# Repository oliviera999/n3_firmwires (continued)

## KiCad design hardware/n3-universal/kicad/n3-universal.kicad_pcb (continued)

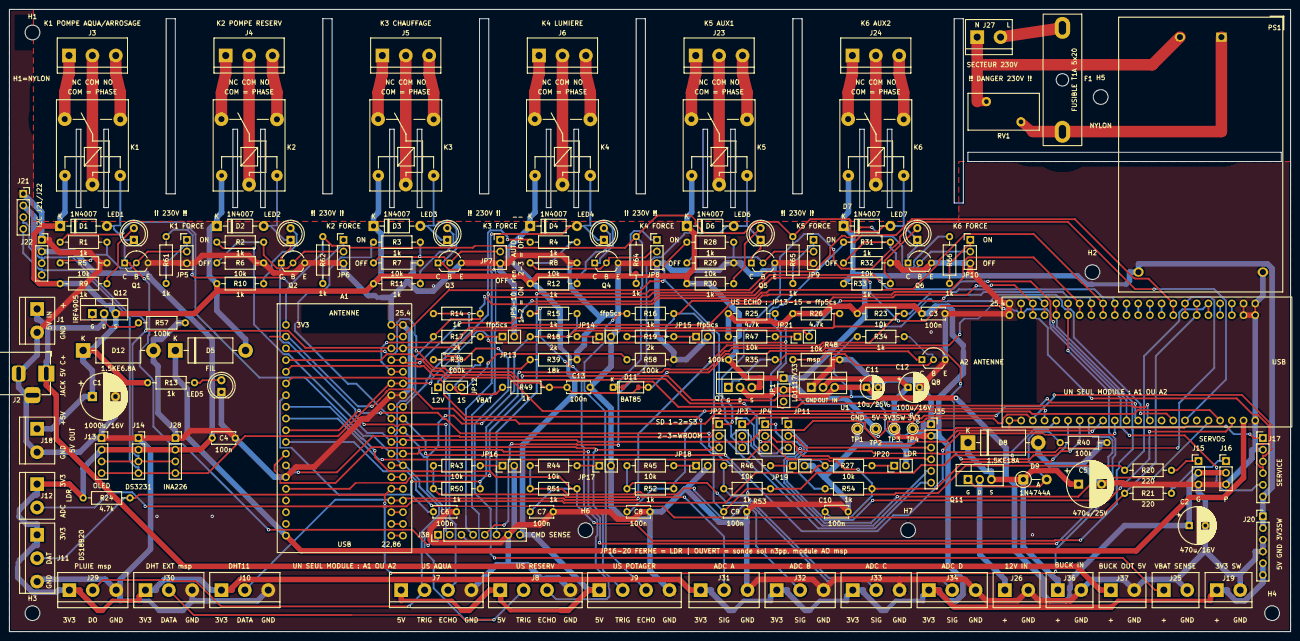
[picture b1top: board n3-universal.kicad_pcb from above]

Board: 2 copper layers, 278.0 x 135.0 mm, 179 parts (0 on the bottom side), 115 nets.

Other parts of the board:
H1, H2, H3, H4, H5, H6, H7: M3; MountingHole_3.2mm_M3

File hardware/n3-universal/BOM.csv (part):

Refs;Qte;Valeur;Empreinte;Description;Source;LCSC;Note achat
A1;1;ESP32 DevKitC 38 broches;ESP32_DevKitC_38pin;Module ESP32-WROOM-32 DevKitC 38 broches, sur 2 supports 1x19 (rangée droite à 25,4 mm, ou 22,86 mm pour un module étroit);;;
A2;1;ESP32-S3-DevKitC-1;ESP32_S3_DevKitC_1_44pin;Site optionnel ESP32-S3-DevKitC-1 44 broches, sur 2 supports 1x22 (rangée droite à 25,4 mm, ou 22,86 mm pour le DevKitC-1 officiel) — un seul module A1 OU A2;Maroc;;Shop4Makers / Moussasoft S3 N16R8 (180 DH) — ne pas importer (ANRT)
C1;1;1000u/16V;CP_Radial_D10.0mm_P5.00mm;Réservoir rail 5V (relais + servos + HC-SR04);Maroc;;électrolytique radial
C10;1;100n;C_Disc_D5.0mm_W2.5mm_P5.00mm;Filtre ADC_E;Maroc;;céramique 100 nF
C11;1;10u/25V;CP_Radial_D5.0mm_P2.50mm;Entrée LDO;Maroc;;électrolytique radial
C12;1;100u/16V;CP_Radial_D6.3mm_P2.50mm;Sortie LDO (stabilité LD1117 : >= 10 µF, électrolytique);Maroc;;électrolytique radial
C13;1;100n;C_Disc_D5.0mm_W2.5mm_P5.00mm;Filtre ADC_VBAT;Maroc;;céramique 100 nF
C2;1;470u/16V;CP_Radial_D8.0mm_P3.50mm;Réservoir du rail 5 V commuté LDO_IN côté servos (appels SG90);Maroc;;électrolytique radial
C3;1;100n;C_Disc_D5.0mm_W2.5mm_P5.00mm;Découplage 3V3 capteurs;Maroc;;céramique 100 nF
C4;1;100n;C_Disc_D5.0mm_W2.5mm_P5.00mm;Découplage 3V3 I2C;Maroc;;céramique 100 nF
C5;1;470u/25V;CP_Radial_D10.0mm_P5.00mm;Réservoir bus 12V protégé;Maroc;;électrolytique radial
C6;1;100n;C_Disc_D5.0mm_W2.5mm_P5.00mm;Filtre ADC ADC_A;Maroc;;céramique 100 nF
C7;1;100n;C_Disc_D5.0mm_W2.5mm_P5.00mm;Filtre ADC ADC_B;Maroc;;céramique 100 nF
C8;1;100n;C_Disc_D5.0mm_W2.5mm_P5.00mm;Filtre ADC ADC_C;Maroc;;céramique 100 nF
C9;1;100n;C_Disc_D5.0mm_W2.5mm_P5.00mm;Filtre ADC ADC_D;Maroc;;céramique 100 nF
D1 D2 D3 D4 D6 D7;6;1N4007;D_DO-41_SOD81_P10.16mm_Horizontal;Diode de roue libre bobine;Maroc / import;C2457;"Moussasoft ; LCSC C2457 (1N4007G MDD) — l'ancien C727 n'existe plus"
D11;1;BAT85;D_DO-35_SOD-123_Dual_P7.62mm;Clamp ADC_VBAT sur +3V3 (panneau branché par erreur sur J25) — empreinte double : BAT85/BAT42/BAT43 DO-35 OU BAT43W/BAT54 SOD-123 (LCSC C19167), un seul des deux posé;import;C19167;"DO-35 épuisé chez LCSC (BAT85 C549292 = 0) → poser la variante SOD-123 BAT43W JSCJ C19167 sur les pads CMS de l'empreinte double ; ou BAT85/BAT42 DO-35 d'une autre source"
D12;1;1.5KE6.8A;D_DO-201AD_P15.24mm_Horizontal;TVS 6,8V (Vrwm 5,8V) sur le rail +5V : surtension / inversion résiduelle;import;C412500;"TVS 6,8 V DO-201 Littelfuse (Vrwm 5,8 V, stock faible) ; repli P6KE6.8A DO-15 C409413 (pattes 0,8 mm, même trou)"
D5;1;FIL;D_DO-201AD_P15.24mm_Horizontal;"PONT DE FIL vers VIN DevKit (rev 0.2.2 : ex-1N5822 court-circuitée, +0,35 V de marge ; ne JAMAIS brancher l'USB du DevKit carte sous tension)";;;
D8;1;1.5KE18A;D_DO-201AD_P15.24mm_Horizontal;TVS 18V transitoires bus batterie (DO-201 : le P6KE est en DO-15, trop fin);import;C1666858;TVS 18 V DO-201 (Littelfuse 1.5KE18A-B) — PAS de 1.5KE15A locale (conduirait à 14,7 V)
D9;1;1N4744A;D_DO-41_SOD81_P5.08mm_Vertical_AnodeUp;Zener 15V grille-source de Q11 (K=source, A=grille) : VGS borné à -15 V;import;C238928;zener 15 V DO-41
F1;1;T1A 5x20;Fuse_5x20_Universal;Fusible entrée secteur du module alim (temporisé 1A) — porte-fusible à capot;import;C3131;porte-fusible 5x20 à capot BLX-A Xucheng C3131 (pas 22,0 ±0,5 mesuré sur sa fiche LCSC, fentes 3 mm de l'empreinte) ou Multicomp MC000830 / Schurter 0031.8201 (22,5-22,6) + cartouche T1A
H1;1;M3;MountingHole_3.2mm_M3;Trou de fixation M3 — H1 : VIS NYLON OBLIGATOIRE (tête métal à <5 mm du 230V);Maroc;;vis M3 (nylon pour H1/H5)
H2 H3 H4 H6 H7;5;M3;MountingHole_3.2mm_M3;Trou de fixation M3;Maroc;;vis M3 (nylon pour H1/H5)
H5;1;M3;MountingHole_3.2mm_M3;Trou de fixation M3 — H5 : VIS NYLON OBLIGATOIRE (entre les pistes N et L du coin secteur);Maroc;;vis M3 (nylon pour H1/H5)
J1;1;Bornier_5.08;TerminalBlock_bornier-2_P5.08mm;Entrée 5V alternative (bornier, 1=+5V 2=GND) — protégée contre l'inversion par Q12;Maroc;;KF128 / KF301 pas 5,08 (Moussasoft 4 DH, Shop4Makers)
J10;1;Bornier_5.08;TerminalBlock_bornier-3_P5.08mm;DHT11/DHT22 (1=3V3 2=DATA 3=GND) — fils nus + embouts;Maroc;;KF128 / KF301 pas 5,08 (Moussasoft 4 DH, Shop4Makers)
J11;1;Bornier_5.08;TerminalBlock_bornier-3_P5.08mm;Sonde DS18B20 étanche (1=3V3 2=DATA 3=GND);Maroc;;KF128 / KF301 pas 5,08 (Moussasoft 4 DH, Shop4Makers)
J12;1;Bornier_5.08;TerminalBlock_bornier-2_P5.08mm;LDR déportée entre 3V3 et l'ADC (1=3V3 2=ADC);Maroc;;KF128 / KF301 pas 5,08 (Moussasoft 4 DH, Shop4Makers)
J13;1;Support OLED;PinSocket_1x04_P2.54mm_Vertical;OLED SSD1306 128x64 I2C 0x3C (1=GND 2=VCC 3=SCL 4=SDA);Maroc;;barrette femelle 2,54 sécable (Moussasoft 6 DH)
J14;1;Support I2C ext;PinSocket_1x04_P2.54mm_Vertical;Extension I2C — ex. module DS3231 (1=GND 2=VCC 3=SCL 4=SDA);Maroc;;barrette femelle 2,54 sécable (Moussasoft 6 DH)
J15;1;Header servo;PinHeader_1x03_P2.54mm_Vertical;Servo GROS (1=SIG 2=LDO_IN 3=GND) — rev 0.2.2 : +5V COMMUTE par Q7 (JP1 fermé = permanent);Maroc;;barrette mâle 2,54 sécable (Moussasoft / Shop4Makers)
J16;1;Header servo;PinHeader_1x03_P2.54mm_Vertical;Servo PETITS (1=SIG 2=LDO_IN 3=GND) — rev 0.2.2 : +5V COMMUTE par Q7 (JP1 fermé = permanent);Maroc;;barrette mâle 2,54 sécable (Moussasoft / Shop4Makers)
J17;1;Header service;PinHeader_1x06_P2.54mm_Vertical;Header service (1=3V3 2=GND 3=EN 4=RX0 5=TX0 6=+5V) — tous les autres GPIO sont consommés par la carte universelle;Maroc;;barrette mâle 2,54 sécable (Moussasoft / Shop4Makers)
J18;1;Bornier_5.08;TerminalBlock_bornier-2_P5.08mm;Distribution 5V (1=+5V 2=GND);Maroc;;KF128 / KF301 pas 5,08 (Moussasoft 4 DH, Shop4Makers)
J19;1;Bornier_5.08;TerminalBlock_bornier-2_P5.08mm;Distribution 3V3 capteurs — rail COMMUTE (1=+3V3_SW 2=GND);Maroc;;KF128 / KF301 pas 5,08 (Moussasoft 4 DH, Shop4Makers)
J2;1;Jack 5.5/2.1;BarrelJack_Horizontal;Entrée 5V (jack DC-005 ~2,5 A, centre = +, ouverture bord gauche);Maroc;;jack DC-005 standard
J20;1;Header alim;PinHeader_1x06_P2.54mm_Vertical;Rail Dupont (1-2=+5V 3-4=GND 5-6=+3V3_SW);Maroc;;barrette mâle 2,54 sécable (Moussasoft / Shop4Makers)
J21;1;Support I2C libre;PinSocket_1x04_P2.54mm_Vertical;Port I2C libre 2 (1=GND 2=VCC 3=SCL 4=SDA);Maroc;;barrette femelle 2,54 sécable (Moussasoft 6 DH)
J22;1;Support I2C libre;PinSocket_1x04_P2.54mm_Vertical;Port I2C libre 3 (1=GND 2=VCC 3=SCL 4=SDA);Maroc;;barrette femelle 2,54 sécable (Moussasoft 6 DH)
J25;1;Bornier_5.08;TerminalBlock_bornier-2_P5.08mm;Sonde batterie (1=VBAT+ 2=GND) — 1S ou bus 12V selon profil;Maroc;;KF128 / KF301 pas 5,08 (Moussasoft 4 DH, Shop4Makers)
J26;1;Bornier_5.08;TerminalBlock_bornier-2_P5.08mm;Entrée bus 12V (1=+12V APRES fusible lame externe 7,5-10A 2=GND);Maroc;;KF128 / KF301 pas 5,08 (Moussasoft 4 DH, Shop4Makers)
J27;1;Bornier_5.08;TerminalBlock_bornier-2_P5.08mm;ENTREE SECTEUR 230V (1=N 2=L) — ZONE DANGER;Maroc;;KF128 / KF301 pas 5,08 (Moussasoft 4 DH, Shop4Makers)
J28;1;Support I2C libre;PinSocket_1x04_P2.54mm_Vertical;Port I2C libre 4 — INA226 (1=GND 2=VCC 3=SCL 4=SDA);Maroc;;barrette femelle 2,54 sécable (Moussasoft 6 DH)
J29;1;Bornier_5.08;TerminalBlock_bornier-3_P5.08mm;Module pluie DO msp (1=3V3_SW 2=DO 3=GND) — net US1, rôles disjoints;Maroc;;KF128 / KF301 pas 5,08 (Moussasoft 4 DH, Shop4Makers)
J23 J24 J3 J4 J5 J6;6;Bornier_5.08;TerminalBlock_bornier-3_P5.08mm;Bornier charge 230V (1=NC 2=COM 3=NO);Maroc;;KF128 / KF301 pas 5,08 (Moussasoft 4 DH, Shop4Makers)
J30;1;Bornier_5.08;TerminalBlock_bornier-3_P5.08mm;DHT externe msp (1=3V3_SW 2=DATA 3=GND) — net US2, rôles disjoints;Maroc;;KF128 / KF301 pas 5,08 (Moussasoft 4 DH, Shop4Makers)
J31;1;Bornier_5.08;TerminalBlock_bornier-3_P5.08mm;Entrée analogique ADC_A (1=3V3_SW 2=SIG 3=GND) — LDR msp / sonde sol n3pp;Maroc;;KF128 / KF301 pas 5,08 (Moussasoft 4 DH, Shop4Makers)
J32;1;Bornier_5.08;TerminalBlock_bornier-3_P5.08mm;Entrée analogique ADC_B (1=3V3_SW 2=SIG 3=GND) — LDR msp / sonde sol n3pp;Maroc;;KF128 / KF301 pas 5,08 (Moussasoft 4 DH, Shop4Makers)
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
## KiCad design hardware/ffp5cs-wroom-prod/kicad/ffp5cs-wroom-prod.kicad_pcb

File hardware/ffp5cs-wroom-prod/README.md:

# Carte porteuse ffp5cs `wroom-prod` (KiCad)

Plan PCB **généré depuis le code du firmware** `ffp5cs` (env PlatformIO `wroom-prod`,
`-DBOARD_WROOM`) : une **carte porteuse (carrier board)** pour module **ESP32 DevKit V1
30 broches** qui intègre tout le câblage aujourd'hui réalisé « en volant » — relais,
adaptation de niveau des HC-SR04, pull-ups, borniers.

> 🔀 **Bi-module depuis la rev 0.6** : la carte offre un **second site A2** pour un
> **ESP32-S3-DevKitC-1 (44 broches)** — on peuple **UN SEUL** module, A1 (WROOM) **ou**
> A2 (S3). Chaque net fonctionnel touche les deux sites ; côté S3 le firmware se
> compile avec `-DPINMAP_S3_CARRIER` (env `wroom-s3-carrier-test`, section carrier de
> `ffp5cs/include/pins.h`). Source de vérité S3 : `pinmap_s3_carrier.json`. Le header
> **J20** expose les GPIO libres du S3 (dont AUX1=IO47 / AUX2=IO42, pendants de J17).
> ⚠️ Ne PAS flasher un env `carrier` sur le système S3 historique câblé main (ni
> l'inverse) : les cartographies diffèrent (corrections strapping/PSRAM/LED RGB).

```
pinmap.json                  Source de vérité site A1 (broches ← ffp5cs/include/pins.h, section WROOM)
pinmap_s3_carrier.json       Source de vérité site A2 (← pins.h, section PINMAP_S3_CARRIER)
kicad/ffp5cs-wroom-prod.kicad_pro / .kicad_sch / .kicad_pcb   Projet KiCad (format v8, ouvrable KiCad 8/9/10)
BOM.csv                      Nomenclature (séparateur ;)
exports/gerbers-*.zip        Fichiers de fabrication (Gerbers + perçages Excellon)
exports/schema.pdf, pcb-*.svg   Rendus pour revue sans KiCad
fritzing/*.fzz               Vue breadboard du câblage (Fritzing >= 1.0)
generator/generate.py        Régénère schéma + PCB (non routé) + BOM depuis pinmap.json
generator/generate_fritzing.py  Régénère le .fzz de câblage
generator/footprints/        Empreintes officielles KiCad 8.0.9 vendorées (+ empreinte DevKit maison)
tools/check_pinmap_vs_firmware.py   Garde anti-dérive code ↔ plan
```

## Ce que couvre la carte (extrait du firmware)

| Fonction (code) | GPIO | Réalisation sur la carte |
|---|---|---|
| `Pins::POMPE_AQUA` (`actuators.h`, actif HAUT) | 16 | Relais K1 SRD-05 + BC337, bornier NO/COM/NC |
| `Pins::POMPE_RESERV` | 18 | Relais K2, idem |
| `Pins::RADIATEURS` | 2 | Relais K3, idem (strapping → pull-down base) |
| `Pins::LUMIERE` | 15 | Relais K4, idem (strapping) |
| `Pins::SERVO_GROS` | 12 | Header servo J15, série 220 Ω + **pull-down 10k obligatoire** (MTDI) |
| `Pins::SERVO_PETITS` | 13 | Header servo J16, série 220 Ω |
| `Pins::ULTRASON_AQUA/TANK/POTA` (mono-broche TRIG=ECHO, `sensor_ultrasonic.cpp`) | 4 / 19 / 33 | JST 4 pts J7-J9, écho 5 V → 3,3 V par pont 1k/2k |
| `Pins::DHT_PIN` (DHT11, `-DUSE_DHT22` en option) | 27 | JST 3 pts J10 + pull-up 10k |
| `Pins::ONE_WIRE_BUS` (DS18B20) | 26 | Bornier J11 + pull-up 4,7k |
| `Pins::LUMINOSITE` (ADC1, entrée seule) | 34 | Bornier J12 pour LDR déportée + 10k vers GND |
| `Pins::I2C_SDA/SCL` — OLED SSD1306 0x3C (`FEATURE_OLED=1`) | 21 / 22 | Support J13 (GND/VCC/SCL/SDA) + pull-ups 4,7k |
| Extension I2C : **3 ports libres** (DS3231, capteurs…) | 21 / 22 | Supports J14, J18, J19 (même brochage GND/VCC/SCL/SDA) |
| GPIO libres (5, 14, 17, 23, 25, 32, 35) + EN | — | Header J17 |

Alimentation : **5 V / 3 A** (jack 5,5/2,1 centre + OU bornier), condensateur réservoir
1000 µF, LED de présence. Le DevKit est alimenté par VIN **à travers une Schottky
1N5822** : on peut brancher l'USB (flash/debug) alim 5 V connectée sans retour de courant.
Les capteurs logiques (DHT, DS18B20, LDR, OLED) sont sur le **3V3 du DevKit** ;
HC-SR04, servos et relais sur le rail 5 V.

## Choix de conception (et pourquoi)

- **Carrier board plutôt que carte à ESP32 soudé** : le module `esp32dev` reste flashable
  par son USB (`pio run -e wroom-prod -t upload`), remplaçable en 10 s, et on évite tout
  le circuit USB-UART/auto-program. 100 % traversant → soudable à la main, fabricable
  partout (JLCPCB/PCBWay, 2 couches, 150 × 100 mm).
- **Relais commandés actif-HAUT** via NPN : conforme à `actuators.h`
  (`on()` → `digitalWrite(HIGH)`). Ne PAS utiliser un module relais du commerce
  actif-BAS sur ces sorties sans adaptation.
- **Broches de strapping** : GPIO2 et GPIO15 (relais) ont un pull-down 10k sur la base du
  transistor → niveau bas au boot, flash série non perturbé. GPIO12 (MTDI, servo gros) a
  un pull-down 10k dédié (R22) : un niveau haut au boot sélectionnerait un VDD_SDIO à
  1,8 V et **brickerait le démarrage**.
- **HC-SR04 en mono-broche** : le firmware pilote TRIG et lit ECHO sur le même GPIO.
  Câblage par canal : GPIO —(direct)— TRIG ; ECHO —1k— GPIO ; GPIO —2k— GND.
  L'écho 5 V est ramené à ~3,3 V, le trigger 3,3 V est accepté par le capteur alimenté en 5 V.
- **GPIO34 entrée seule, sans pull-up interne** : pont diviseur LDR obligatoire sur la
  carte (LDR déportée entre 3V3 et l'entrée, 10k vers GND).
- **RX0/TX0 laissés libres** (non routés) : réservés à l'USB-UART du module.
- **3 ports I2C libres** (J14/J18/J19) en plus de l'OLED : avec les pull-ups 4,7 k
  déjà en place, 3-4 modules simultanés sont confortables (adresses différentes,
  bus total < ~50 cm) — au-delà, réduire les pull-ups à 2,2 k.

## À vérifier avant fabrication (limites connues)

1. **Entraxe des modules** : l'empreinte A1 suppose un DevKit V1 **30 broches, rangées
   espacées de 25,4 mm** (2 × supports 1×15). Mesurer votre exemplaire ; les variantes
   38 broches (DevKitC) ont un autre brochage → adapter `generate.py` (table `DEVKIT_A/B`).
   L'empreinte A2 suppose un ESP32-S3-DevKitC-1 **44 broches, rangées espacées de
   22,86 mm** (2 × supports 1×22) — vérifier entraxe ET ordre des broches sur
   l'exemplaire réel (tables `S3_LEFT/S3_RIGHT`) avant de souder les supports.
2. **Routage (rev 0.6, dimensionné 12/24 V)** : PCB routé par `generator/route_lv.py`
   (freerouting + vias de couture GND + reliefs thermiques) avec des
   **classes de nets** — contacts relais NO/COM/NC en **2 mm** (≈ 5-6 A continus en
   cuivre 1 oz, marge correcte jusqu'à ~8 A en pointe), rails +5V/VIN/GND en
   **1,2 mm**, signaux 0,4 mm. DRC KiCad 8 : 0 violation, 0 non-connecté ; Gerbers
   dans `exports/`. **Le 230 V reste interdit sur cette carte** (isolement non prévu :
   plans de masse proches des contacts, pas de fentes ni de zone secteur dédiée) —
   la sérigraphie le rappelle près des borniers. Pour du secteur, piloter des modules
   relais/contacteurs 230 V déportés. NB : `generate.py` régénère un PCB **non
   routé** — ne pas régénérer par-dessus `kicad/` sans vouloir perdre le routage.
3. **Relais NO/NC** : mapping issu du couple symbole/empreinte officiel KiCad
   (SANYOU SRD Form C : bobine 2-5, COM 1, NO 3, NC 4). Contrôler à l'ohmmètre au
   premier montage avant de brancher une charge.
4. **ERC/DRC** : les étiquettes locales alimentent les nets (pas de power-flags) ; l'ERC
   émet des avertissements « input power pin not driven », sans conséquence.

## Corrections rev 0.5

- **Supports du DevKit dans la BOM** (ligne « A1 (supports) » : 2 barrettes femelles
  1×15) — jusque-là seulement mentionnés en description.
- **Zone dégagée sous l'antenne WiFi** : keepout cuivre (pistes/vias/pour) sur les
  deux faces sous le débord antenne du module, note sérigraphiée déplacée côté antenne.
- **Checker étendu** : `tools/check_pinmap_vs_firmware.py` fige désormais aussi la
  topologie des canaux HC-SR04 (JST 1=+5V 2=GPIO 3=ECHO 4=GND, 1 k série écho,
  2 k pull-down) — le câblage capteur ne peut plus dériver silencieusement.
- GPIO 23/25 : déclarés `AUX1`/`AUX2` dans `pinmap.json` (firmware ≥ v15.26) ; sur
  cette carte ils restent en breakout J17 (piloter des modules relais externes) —
  les relais AUX embarqués sont sur la variante 230 V.

## Vue Fritzing (câblage de prototype)

`fritzing/ffp5cs-wroom-prod-cablage.fzz` (Fritzing ≥ 1.0) montre le **câblage
breadboard** périphériques ↔ DevKit : HC-SR04 + ponts 1k/2k, DS18B20, LDR, servos,
pull-ups, avec le code couleur rouge = 5 V, orange = 3V3, noir = GND. Le DevKit, le
DHT11, l'OLED et les sorties relais sont figurés par des **headers génériques
étiquetés** (pas de pièce core fidèle dans Fritzing) — survoler une pièce affiche son
titre avec l'ordre des broches. Fichier vérifié à l'ouverture (« Routing completed »,
aucune pièce manquante) ; les positions se réarrangent librement, les connexions
suivent. Le projet KiCad reste la référence pour la fabrication.

## Régénérer / vérifier

```bash
cd hardware/ffp5cs-wroom-prod
python3 generator/generate.py                 # schéma + PCB placé (NON routé) + BOM
python3 generator/route_lv.py                 # routage complet + vérifications
python3 generator/tidy_silkscreen.py   # sérigraphie : repères vs étiquettes
python3 generator/export_fab.py        # zip Gerbers prêt JLCPCB
python3 tools/check_pinmap_vs_firmware.py     # cohérence pins.h (WROOM) ↔ pinmap ↔ schéma ↔ PCB
```

Toute modification de `ffp5cs/include/pins.h` (section WROOM) doit être répercutée dans
`pinmap.json` puis régénérée — le checker échoue (exit ≠ 0) tant que les trois ne sont
pas alignés. ⚠️ La régénération **écrase** `kicad/` : une fois le routage manuel commencé,
faire les retouches dans KiCad et cesser de régénérer (ou porter les retouches dans
`generate.py`).

## Licences

Les empreintes de `generator/footprints/` proviennent de la
[bibliothèque officielle KiCad](https://gitlab.com/kicad/libraries/kicad-footprints)
(tag 8.0.9), licence CC-BY-SA 4.0 avec exception d'usage pour les designs ;
`ESP32_DevKit_V1_30pin.kicad_mod` est généré par `generate.py`.

Commander la carte : voir **[../COMMANDE_JLCPCB.md](../COMMANDE_JLCPCB.md)**.

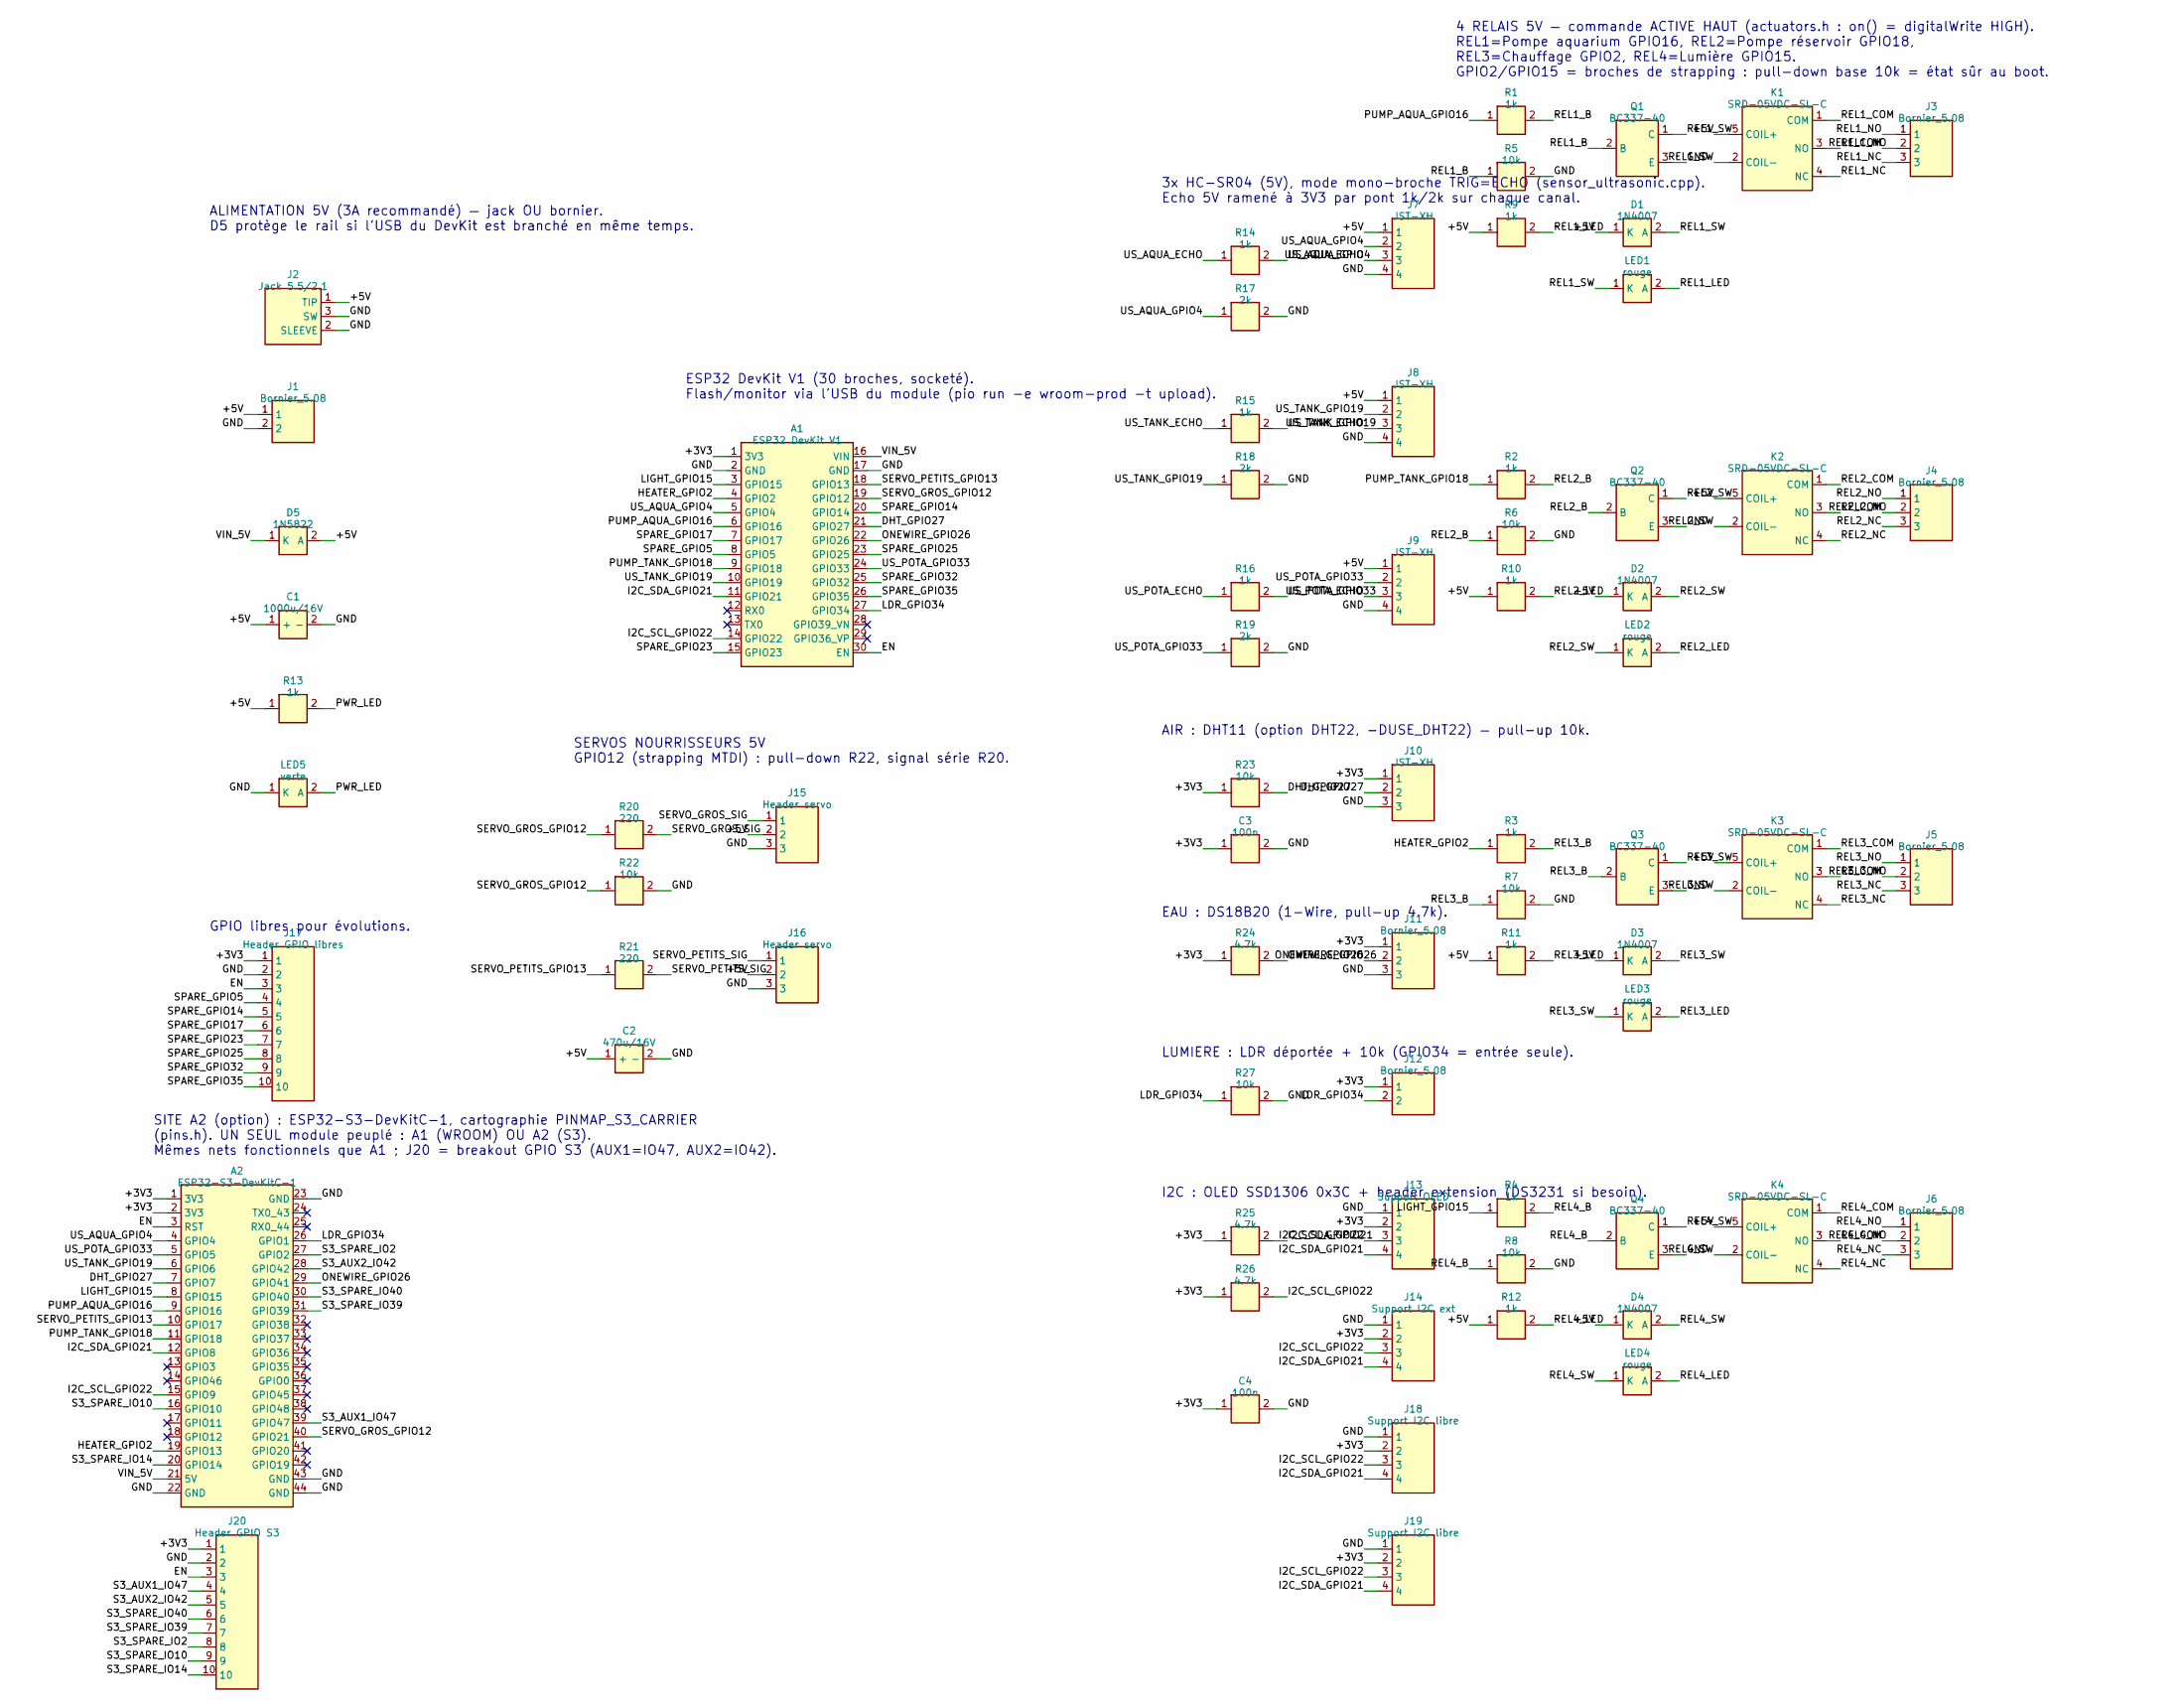
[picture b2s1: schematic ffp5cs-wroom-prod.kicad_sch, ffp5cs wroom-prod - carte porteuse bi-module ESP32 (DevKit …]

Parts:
A1: ESP32 DevKit V1; ESP32_DevKit_V1_30pin
A2: ESP32-S3-DevKitC-1; ESP32_S3_DevKitC_1_44pin
C1: 1000u/16V; CP_Radial_D10.0mm_P5.00mm
C2: 470u/16V; CP_Radial_D8.0mm_P3.50mm
C3, C4: 100n; C_Disc_D5.0mm_W2.5mm_P5.00mm
D1, D2, D3, D4: 1N4007; D_DO-41_SOD81_P10.16mm_Horizontal
D5: 1N5822; D_DO-201AD_P15.24mm_Horizontal
J1, J12: Bornier_5.08; TerminalBlock_bornier-2_P5.08mm
J2: Jack 5.5/2.1; BarrelJack_Horizontal
J3, J4, J5, J6, J11: Bornier_5.08; TerminalBlock_bornier-3_P5.08mm
J7, J8, J9: JST-XH; JST_XH_B4B-XH-A_1x04_P2.50mm_Vertical
J10: JST-XH; JST_XH_B3B-XH-A_1x03_P2.50mm_Vertical
J13: Support OLED; PinSocket_1x04_P2.54mm_Vertical
J14: Support I2C ext; PinSocket_1x04_P2.54mm_Vertical
J15, J16: Header servo; PinHeader_1x03_P2.54mm_Vertical
J17: Header GPIO libres; PinHeader_1x10_P2.54mm_Vertical
J18, J19: Support I2C libre; PinSocket_1x04_P2.54mm_Vertical
J20: Header GPIO S3; PinHeader_1x10_P2.54mm_Vertical
K1, K2, K3, K4: SRD-05VDC-SL-C; Relay_SPDT_SANYOU_SRD_Series_Form_C
LED1, LED2, LED3, LED4: rouge; LED_D5.0mm
LED5: verte; LED_D5.0mm
Q1, Q2, Q3, Q4: BC337-40; TO-92_Inline
R1, R2, R3, R4, R9, R10, R11, R12, R13, R14, R15, R16: 1k; R_Axial_DIN0207_L6.3mm_D2.5mm_P10.16mm_Horizontal
R5, R6, R7, R8, R22, R23, R27: 10k; R_Axial_DIN0207_L6.3mm_D2.5mm_P10.16mm_Horizontal
R17, R18, R19: 2k; R_Axial_DIN0207_L6.3mm_D2.5mm_P10.16mm_Horizontal
R20, R21: 220; R_Axial_DIN0207_L6.3mm_D2.5mm_P10.16mm_Horizontal
R24, R25, R26: 4.7k; R_Axial_DIN0207_L6.3mm_D2.5mm_P10.16mm_Horizontal

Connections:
+3V3: A1.1 (3V3), A2.1 (3V3), A2.2 (3V3), C3.1, C4.1, J10.1, J11.1, J12.1, J13.2, J14.2, J17.1, J18.2, J19.2, J20.1, R23.1, R24.1, R25.1, R26.1
+5V: C1.1 (+), C2.1 (+), D1.1 (K), D2.1 (K), D3.1 (K), D4.1 (K), D5.2 (A), J1.1, J2.1 (TIP), J7.1, J8.1, J9.1, J15.2, J16.2, K1.5 (COIL+), K2.5 (COIL+), K3.5 (COIL+), K4.5 (COIL+), R9.1, R10.1, R11.1, R12.1, R13.1
DHT_GPIO27: A1.21 (GPIO27), A2.7 (GPIO7), J10.2, R23.2
EN: A1.30 (EN), A2.3 (RST), J17.3, J20.3
GND: A1.2 (GND), A1.17 (GND), A2.22 (GND), A2.23 (GND), A2.43 (GND), A2.44 (GND), C1.2 (-), C2.2 (-), C3.2, C4.2, J1.2, J2.2 (SLEEVE), J2.3 (SW), J7.4, J8.4, J9.4, J10.3, J11.3, J13.1, J14.1, J15.3, J16.3, J17.2, J18.1, J19.1, J20.2, LED5.1 (K), Q1.3 (E), Q2.3 (E), Q3.3 (E), Q4.3 (E), R5.2, R6.2, R7.2, R8.2, R17.2, R18.2, R19.2, R22.2, R27.2
HEATER_GPIO2: A1.4 (GPIO2), A2.19 (GPIO13), R3.1
I2C_SCL_GPIO22: A1.14 (GPIO22), A2.15 (GPIO9), J13.3, J14.3, J18.3, J19.3, R26.2
I2C_SDA_GPIO21: A1.11 (GPIO21), A2.12 (GPIO8), J13.4, J14.4, J18.4, J19.4, R25.2
LDR_GPIO34: A1.27 (GPIO34), A2.26 (GPIO1), J12.2, R27.1
LIGHT_GPIO15: A1.3 (GPIO15), A2.8 (GPIO15), R4.1
ONEWIRE_GPIO26: A1.22 (GPIO26), A2.29 (GPIO41), J11.2, R24.2
PUMP_AQUA_GPIO16: A1.6 (GPIO16), A2.9 (GPIO16), R1.1
PUMP_TANK_GPIO18: A1.9 (GPIO18), A2.11 (GPIO18), R2.1
PWR_LED: LED5.2 (A), R13.2
REL1_B: Q1.2 (B), R1.2, R5.1
REL1_COM: J3.2, K1.1 (COM)
REL1_LED: LED1.2 (A), R9.2
REL1_NC: J3.3, K1.4 (NC)
REL1_NO: J3.1, K1.3 (NO)
REL1_SW: D1.2 (A), K1.2 (COIL-), LED1.1 (K), Q1.1 (C)
REL2_B: Q2.2 (B), R2.2, R6.1
REL2_COM: J4.2, K2.1 (COM)
REL2_LED: LED2.2 (A), R10.2
REL2_NC: J4.3, K2.4 (NC)
REL2_NO: J4.1, K2.3 (NO)
REL2_SW: D2.2 (A), K2.2 (COIL-), LED2.1 (K), Q2.1 (C)
REL3_B: Q3.2 (B), R3.2, R7.1
REL3_COM: J5.2, K3.1 (COM)
REL3_LED: LED3.2 (A), R11.2
REL3_NC: J5.3, K3.4 (NC)
REL3_NO: J5.1, K3.3 (NO)
REL3_SW: D3.2 (A), K3.2 (COIL-), LED3.1 (K), Q3.1 (C)
REL4_B: Q4.2 (B), R4.2, R8.1
REL4_COM: J6.2, K4.1 (COM)
REL4_LED: LED4.2 (A), R12.2
REL4_NC: J6.3, K4.4 (NC)
REL4_NO: J6.1, K4.3 (NO)
REL4_SW: D4.2 (A), K4.2 (COIL-), LED4.1 (K), Q4.1 (C)
S3_AUX1_IO47: A2.39 (GPIO47), J20.4
S3_AUX2_IO42: A2.28 (GPIO42), J20.5
S3_SPARE_IO2: A2.27 (GPIO2), J20.8
S3_SPARE_IO10: A2.16 (GPIO10), J20.9
S3_SPARE_IO14: A2.20 (GPIO14), J20.10
S3_SPARE_IO39: A2.31 (GPIO39), J20.7
S3_SPARE_IO40: A2.30 (GPIO40), J20.6
SERVO_GROS_GPIO12: A1.19 (GPIO12), A2.40 (GPIO21), R20.1, R22.1
SERVO_GROS_SIG: J15.1, R20.2
SERVO_PETITS_GPIO13: A1.18 (GPIO13), A2.10 (GPIO17), R21.1
SERVO_PETITS_SIG: J16.1, R21.2
SPARE_GPIO5: A1.8 (GPIO5), J17.4
SPARE_GPIO14: A1.20 (GPIO14), J17.5
SPARE_GPIO17: A1.7 (GPIO17), J17.6
SPARE_GPIO23: A1.15 (GPIO23), J17.7
SPARE_GPIO25: A1.23 (GPIO25), J17.8
SPARE_GPIO32: A1.25 (GPIO32), J17.9
SPARE_GPIO35: A1.26 (GPIO35), J17.10
US_AQUA_ECHO: J7.3, R14.1
US_AQUA_GPIO4: A1.5 (GPIO4), A2.4 (GPIO4), J7.2, R14.2, R17.1
US_POTA_ECHO: J9.3, R16.1
US_POTA_GPIO33: A1.24 (GPIO33), A2.5 (GPIO5), J9.2, R16.2, R19.1
US_TANK_ECHO: J8.3, R15.1
US_TANK_GPIO19: A1.10 (GPIO19), A2.6 (GPIO6), J8.2, R15.2, R18.1
VIN_5V: A1.16 (VIN), A2.21 (5V), D5.1 (K)

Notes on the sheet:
ALIMENTATION 5V (3A recommandé) — jack OU bornier. D5 protège le rail si l'USB du DevKit est branché en même temps.
ESP32 DevKit V1 (30 broches, socketé). Flash/monitor via l'USB du module (pio run -e wroom-prod -t upload).
SERVOS NOURRISSEURS 5V GPIO12 (strapping MTDI) : pull-down R22, signal série R20.
3x HC-SR04 (5V), mode mono-broche TRIG=ECHO (sensor_ultrasonic.cpp). Echo 5V ramené à 3V3 par pont 1k/2k sur chaque canal.
AIR : DHT11 (option DHT22, -DUSE_DHT22) — pull-up 10k.
EAU : DS18B20 (1-Wire, pull-up 4.7k).
LUMIERE : LDR déportée + 10k (GPIO34 = entrée seule).
I2C : OLED SSD1306 0x3C + header extension (DS3231 si besoin).
4 RELAIS 5V — commande ACTIVE HAUT (actuators.h : on() = digitalWrite HIGH). REL1=Pompe aquarium GPIO16, REL2=Pompe réservoir GPIO18, REL3=Chauffage GPIO2, REL4=Lumière GPIO15. GPIO2/GPIO15 = broches de strapping : pull-down base 10k = état sûr au boot.
GPIO libres pour évolutions.
SITE A2 (option) : ESP32-S3-DevKitC-1, cartographie PINMAP_S3_CARRIER (pins.h). UN SEUL module peuplé : A1 (WROOM) OU A2 (S3). Mêmes nets fonctionnels que A1 ; J20 = breakout GPIO S3 (AUX1=IO47, AUX2=IO42).

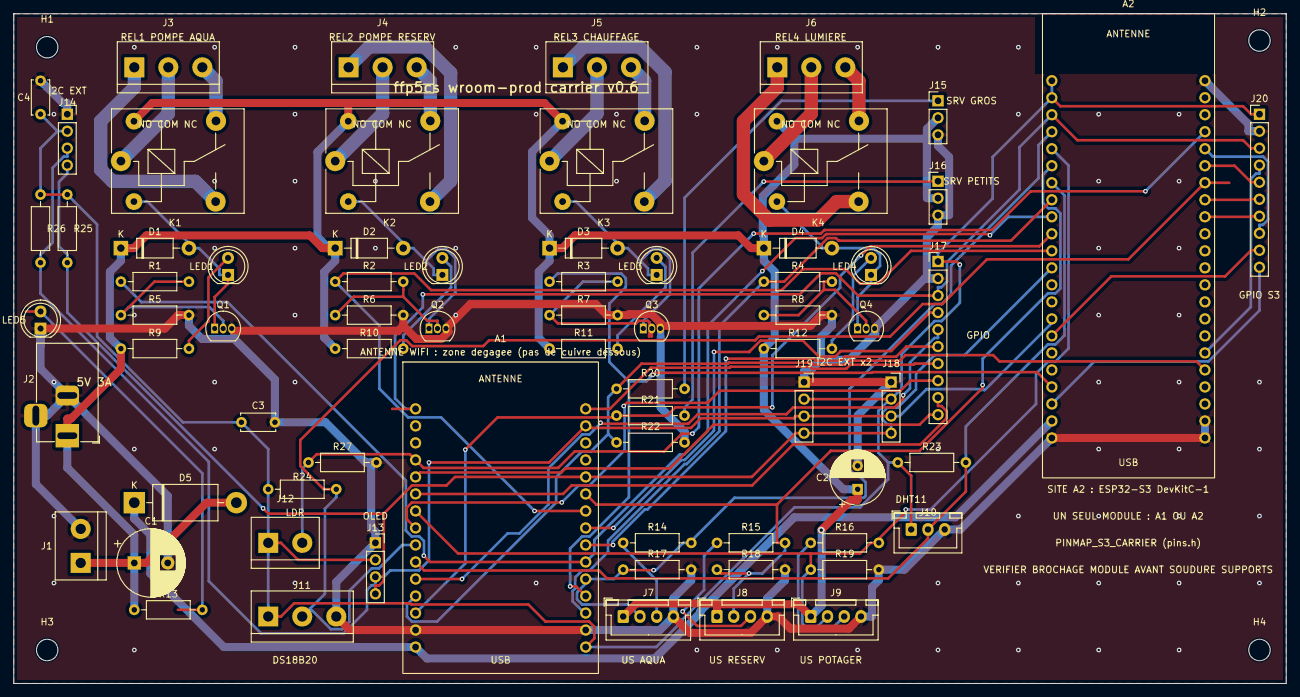
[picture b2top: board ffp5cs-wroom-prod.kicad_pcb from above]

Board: 2 copper layers, 190.0 x 100.0 mm, 75 parts (0 on the bottom side), 63 nets.

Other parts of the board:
H1, H2, H3, H4: M3; MountingHole_3.2mm_M3

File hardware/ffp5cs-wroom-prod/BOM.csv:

Refs;Qte;Valeur;Empreinte;Description
A1;1;ESP32 DevKit V1;ESP32_DevKit_V1_30pin;Module ESP32-WROOM-32 DevKit V1 30 broches, sur 2 supports 1x15
A2;1;ESP32-S3-DevKitC-1;ESP32_S3_DevKitC_1_44pin;Site optionnel ESP32-S3-DevKitC-1 44 broches, sur 2 supports 1x22 (un seul module A1 OU A2)
C1;1;1000u/16V;CP_Radial_D10.0mm_P5.00mm;Réservoir rail 5V (relais + servos + HC-SR04)
C2;1;470u/16V;CP_Radial_D8.0mm_P3.50mm;Découplage rail 5V servos
C3;1;100n;C_Disc_D5.0mm_W2.5mm_P5.00mm;Découplage 3V3 capteurs
C4;1;100n;C_Disc_D5.0mm_W2.5mm_P5.00mm;Découplage 3V3 I2C
D1 D2 D3 D4;4;1N4007;D_DO-41_SOD81_P10.16mm_Horizontal;Diode de roue libre bobine
D5;1;1N5822;D_DO-201AD_P15.24mm_Horizontal;Schottky 3A vers VIN DevKit (anti-retour si USB branché)
H1 H2 H3 H4;4;M3;MountingHole_3.2mm_M3;Trou de fixation M3
J1;1;Bornier_5.08;TerminalBlock_bornier-2_P5.08mm;Entrée 5V alternative (bornier, 1=+5V 2=GND)
J10;1;JST-XH;JST_XH_B3B-XH-A_1x03_P2.50mm_Vertical;DHT11/DHT22 (1=3V3 2=DATA 3=GND)
J11;1;Bornier_5.08;TerminalBlock_bornier-3_P5.08mm;Sonde DS18B20 étanche (1=3V3 2=DATA 3=GND)
J12;1;Bornier_5.08;TerminalBlock_bornier-2_P5.08mm;LDR déportée entre 3V3 et l'ADC (1=3V3 2=ADC)
J13;1;Support OLED;PinSocket_1x04_P2.54mm_Vertical;OLED SSD1306 128x64 I2C 0x3C (1=GND 2=VCC 3=SCL 4=SDA)
J14;1;Support I2C ext;PinSocket_1x04_P2.54mm_Vertical;Extension I2C — ex. module DS3231 (1=GND 2=VCC 3=SCL 4=SDA)
J15;1;Header servo;PinHeader_1x03_P2.54mm_Vertical;Servo GROS (1=SIG 2=+5V 3=GND)
J16;1;Header servo;PinHeader_1x03_P2.54mm_Vertical;Servo PETITS (1=SIG 2=+5V 3=GND)
J17;1;Header GPIO libres;PinHeader_1x10_P2.54mm_Vertical;GPIO libres (1=3V3 2=GND 3=EN 4=IO5 5=IO14 6=IO17 7=IO23 8=IO25 9=IO32 10=IO35)
J18;1;Support I2C libre;PinSocket_1x04_P2.54mm_Vertical;Port I2C libre 2 (1=GND 2=VCC 3=SCL 4=SDA)
J19;1;Support I2C libre;PinSocket_1x04_P2.54mm_Vertical;Port I2C libre 3 (1=GND 2=VCC 3=SCL 4=SDA)
J2;1;Jack 5.5/2.1;BarrelJack_Horizontal;Entrée 5V 3A (jack, centre = +)
J20;1;Header GPIO S3;PinHeader_1x10_P2.54mm_Vertical;GPIO libres site S3 (1=3V3 2=GND 3=EN 4=IO47/AUX1 5=IO42/AUX2 6=IO40 7=IO39 8=IO2 9=IO10 10=IO14)
J3 J4 J5 J6;4;Bornier_5.08;TerminalBlock_bornier-3_P5.08mm;Bornier charge (1=NO 2=COM 3=NC)
J7;1;JST-XH;JST_XH_B4B-XH-A_1x04_P2.50mm_Vertical;HC-SR04 AQUA (1=5V 2=TRIG 3=ECHO 4=GND)
J8;1;JST-XH;JST_XH_B4B-XH-A_1x04_P2.50mm_Vertical;HC-SR04 TANK (1=5V 2=TRIG 3=ECHO 4=GND)
J9;1;JST-XH;JST_XH_B4B-XH-A_1x04_P2.50mm_Vertical;HC-SR04 POTA (1=5V 2=TRIG 3=ECHO 4=GND)
K1 K2 K3 K4;4;SRD-05VDC-SL-C;Relay_SPDT_SANYOU_SRD_Series_Form_C;Relais 5V SPDT 10A (Songle/Sanyou SRD)
LED1 LED2 LED3 LED4;4;rouge;LED_D5.0mm;LED témoin relais ON
LED5;1;verte;LED_D5.0mm;LED présence 5V
Q1 Q2 Q3 Q4;4;BC337-40;TO-92_Inline;Transistor NPN commande relais (1=C 2=B 3=E)
R1 R2 R3 R4;4;1k;R_Axial_DIN0207_L6.3mm_D2.5mm_P10.16mm_Horizontal;Résistance base transistor
R13;1;1k;R_Axial_DIN0207_L6.3mm_D2.5mm_P10.16mm_Horizontal;Résistance LED présence 5V
R14;1;1k;R_Axial_DIN0207_L6.3mm_D2.5mm_P10.16mm_Horizontal;Série écho HC-SR04 AQUA
R15;1;1k;R_Axial_DIN0207_L6.3mm_D2.5mm_P10.16mm_Horizontal;Série écho HC-SR04 TANK
R16;1;1k;R_Axial_DIN0207_L6.3mm_D2.5mm_P10.16mm_Horizontal;Série écho HC-SR04 POTA
R17;1;2k;R_Axial_DIN0207_L6.3mm_D2.5mm_P10.16mm_Horizontal;Pont diviseur écho AQUA (5V->3V3)
R18;1;2k;R_Axial_DIN0207_L6.3mm_D2.5mm_P10.16mm_Horizontal;Pont diviseur écho TANK (5V->3V3)
R19;1;2k;R_Axial_DIN0207_L6.3mm_D2.5mm_P10.16mm_Horizontal;Pont diviseur écho POTA (5V->3V3)
R20;1;220;R_Axial_DIN0207_L6.3mm_D2.5mm_P10.16mm_Horizontal;Série signal servo gros
R21;1;220;R_Axial_DIN0207_L6.3mm_D2.5mm_P10.16mm_Horizontal;Série signal servo petits
R22;1;10k;R_Axial_DIN0207_L6.3mm_D2.5mm_P10.16mm_Horizontal;Pull-down GPIO12 (strapping MTDI : doit être bas au boot)
R23;1;10k;R_Axial_DIN0207_L6.3mm_D2.5mm_P10.16mm_Horizontal;Pull-up data DHT11
R24;1;4.7k;R_Axial_DIN0207_L6.3mm_D2.5mm_P10.16mm_Horizontal;Pull-up bus 1-Wire DS18B20
R25;1;4.7k;R_Axial_DIN0207_L6.3mm_D2.5mm_P10.16mm_Horizontal;Pull-up I2C SDA
R26;1;4.7k;R_Axial_DIN0207_L6.3mm_D2.5mm_P10.16mm_Horizontal;Pull-up I2C SCL
R27;1;10k;R_Axial_DIN0207_L6.3mm_D2.5mm_P10.16mm_Horizontal;Bas du pont diviseur LDR (GPIO34 = entrée seule ADC)
R5 R6 R7 R8;4;10k;R_Axial_DIN0207_L6.3mm_D2.5mm_P10.16mm_Horizontal;Pull-down base (état sûr au boot)
R10 R11 R12 R9;4;1k;R_Axial_DIN0207_L6.3mm_D2.5mm_P10.16mm_Horizontal;Résistance LED témoin
A1 (supports);2;Support femelle 1x15 P2.54;monte sur l'empreinte ESP32_DevKit_V1_30pin;Barrettes femelles 15 pts : le DevKit s'enfiche, jamais soudé
A2 (supports);2;Support femelle 1x22 P2.54;monte sur l'empreinte ESP32_S3_DevKitC_1_44pin;Barrettes femelles 22 pts (site S3 optionnel) : à souder seulement si un S3-DevKitC-1 est prévu

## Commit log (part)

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2026-06-09 refactor(ffp5cs): extrait postSenderTask d'app_tasks (app_tasks_post.cpp)
    postSenderTask (envoi fire-and-forget POST/heartbeat) -> app_tasks_post.cpp.
    PostSenderType/PostSenderMsg déplacés dans app_tasks_internal.h (partagés
    producteur netTask / consommateur postSenderTask) ; g_postSenderQueue passé
    en linkage externe. app_tasks.cpp : 1163 -> 1098 lignes.
    Cumul refonte (pool+web+sensor+mail+ota+post) : 1788 -> 1098 (-39%).
    Build wroom-test OK.
2026-06-09 fix(build): vrai build Linux/CI (pio_repair_build_junction sys.exit) + erreurs de compilation exposées
    CRITIQUE : scripts/pio_repair_build_junction.py faisait sys.exit(0) sur les
    plateformes sans redirection (Linux/CI), terminant 'pio run' AVANT la
    compilation -> le build 'reussissait' sans rien compiler. Donc la CI ffp5cs
    (et les builds locaux) etaient vacants : mes refactors n'avaient jamais ete
    compiles. Corrige avec le meme motif 'if root:' que pio_redirect_build_dir.py
    (Windows inchange, Linux/CI compile vraiment).
2026-06-09 ci(ffp5cs): budget flash wroom-prod 98% (partition fs_mail ~96%)
2026-06-09 docs(ffp5cs): chiffres flash réels + seuil prod 85% (DRAM = vraie contrainte)
    Build prod réel (mesuré) : flash 78,7% (partition fs_mail), pas ~96% comme
    estimé. La vraie tension de wroom-prod est la DRAM interne (~99,9%, ~108 o
    libres), gérée par le linker — pas le flash. Seuil flash prod 98% -> 85%
    (marge anti-régression réaliste). Investigation nm : décomposition neutre
    en .bss (pas de duplication), donc non responsable de la marge DRAM.
2026-06-09 refactor(ffp5cs): extrait la logique refill d'automatism.cpp (1519 -> 1224)
    8 méthodes handleRefill* (sécurités trop-plein/niveau-bas, démarrage/arrêt
    auto, durée max, récupération) -> automatism/automatism_refill.cpp (suit le
    pattern src/automatism/ existant ; méthodes membres, comportement identique,
    self-contained : aucun global de fichier). WIP : validation build en cours.
2026-06-09 docs(ffp5cs): bilan découpe god-files (6) + volet String résolu
2026-06-09 refactor(ffp5cs): scinde ota_manager_download.cpp (1362 -> 911)
    downloadFirmwareUltraRevolutionary (fallback micro-chunks) + downloadFilesystem
    (image LittleFS) déplacés vers ota_manager_download_alt.cpp. Méthodes membres
    OTAManager (aucun static/anon-namespace de fichier), bloc d'includes identique.
    Build wroom-test OK. Plus aucun .cpp ffp5cs au-dessus de 1000 lignes.
2026-06-10 [ffp5cs] corrige pertes post reveil ota
2026-06-12 perf(poissonglouton): détection US filtrée sur front, debounce 600 ms, persist NVS lazy, sleep adaptatif nuit/batterie
    - Ultrason : 2 polls consécutifs sous le seuil requis (rejette les échos
    isolés) et déclenchement sur front — l'objet doit sortir du champ avant
    un nouveau comptage, comme l'IR.
    - Debounce global 1500 -> 600 ms : les deux capteurs étant désormais sur
    front, le debounce long ne servait plus qu'à bloquer les bouteilles
    rapprochées (perte ~1/3 à débit soutenu).
2026-06-13 chore(ffp5cs): purge artefacts versionnés et durcit .gitignore
    Retire du suivi git ~418 Mo d'artefacts régénérés ou parasites qui
    n'ont aucun rôle dans le build (framework Arduino via PlatformIO ;
    managed_components/ n'est référencé ni par src/, ni par CMakeLists.txt,
    ni par platformio.ini, ni par la CI).
    - managed_components/ (3404 fichiers, ~398 Mo) : composants ESP-IDF
    récupérés par le component manager, non utilisés par le build Arduino.
2026-06-13 test(ffp5cs): suite native verrouillant le contrat de corps POST HMAC
    Ajoute test/test_post_body/ (Unity, hôte) couvrant Ffp3PostBody::buildFullUpdateBody
    et applyExtraPairs — une des fonctions pures prioritaires de l'audit §3.8, jusqu'ici
    non testée.
    Le corps produit est signé HMAC par le firmware puis reconstruit côté serveur par
    App\Security\Ffp3HmacPostBody::buildFromParams() pour vérifier la signature : l'ordre
    des champs et le format doivent rester strictement identiques des deux côtés, sinon
2026-06-13 test(ffp5cs): complète la couverture du corps POST HMAC (Ffp3PostBody)
    +6 cas sur les trous du contrat firmware<->serveur :
    - capacité des extras (8 max) : overflow ignoré sans débordement
    - bloc suffixe émis après les extras, dans l'ordre serveur fixe
    - parsing applyExtraPairs : segment sans '=', clé vide, segments vides (&&)
    - CARACTÉRISATION d'une divergence potentielle (S1/S2) : un extra à valeur
    vide ('foo=') est ÉMIS, alors que les champs principaux vides sont OMIS.
2026-06-13 test(ffp5cs): stub FreeRTOS natif + couvre la normalisation d'URL OTA
    Débloque le test natif de la logique dépendante de config.h, jusqu'ici
    impossible (config.h -> config_tasks.h -> <freertos/FreeRTOS.h>).
    Infra (test-only, sans impact sur le build firmware qui n'inclut pas test/unit/) :
    - test/unit/freertos/{FreeRTOS,task}.h : stub minimal (UBaseType_t/BaseType_t/
    TickType_t/TaskHandle_t + macros) — juste ce que config_tasks.h exige pour
    ses constexpr de priorité/cœur.
2026-06-14 test(ffp5cs): couvre getServerHostname + getOutputUrl (server_url_config)
    Complète test_server_url : getServerHostname (extraction d'hôte avec parsing
    réel — strip scheme http(s)://, arrêt à ':'/'/' + bornage) et getOutputUrl
    étaient non testés.
    +5 tests : extraction hôte (scheme+port retirés), gardes (null, size 0),
    troncature sans débordement, getOutputUrl bien formé (base + pas de // après
    schéma).
2026-06-14 refactor(ffp5cs): extrait + teste la validation d'epoch (audit 3.8)
    Extrait isValidEpoch (validation NON SIGNÉE anti-overflow : EPOCH_MAX_VALID
    2050 > INT32_MAX, donc comparaison en unsigned obligatoire sur time_t 32-bit)
    et epochAbsDiff de power.cpp vers include/epoch_util.h. Bug-prone et pervasif
    (validation NTP/RTC à 7 endroits) ; un mauvais traitement du dépassement
    INT32_MAX ferait rejeter des horloges valides.
    - include/epoch_util.h : namespace EpochUtil, logique paramétrée (bornes en
2026-06-15 test(ffp5cs): couvre les conversions cm<->mm (seuils d'alerte)
    SensorConfig::Ultrasonic::cmToMm / mmToCmRounded (config_sensors.h) n'étaient
    pas testées alors qu'elles sous-tendent TOUS les seuils d'alerte de niveau
    d'eau (comparaisons mm capteur <-> cm config dans automatism_display.cpp).
    Un bug y fausserait silencieusement tous les déclenchements.
    +3 tests (test pur, aucune modif firmware) :
    - cmToMm (0/1/18/80/1234) ;
2026-06-15 refactor(ffp5cs): C4 étape 2 — extrait ReservoirLowSecurity (debounce+hystérésis réserve basse, pur + tests)
    Deuxième petite extraction de la god-class Automatism, même patron que FloodAlert,
    comportement strictement identique (parité ligne à ligne).
    - Nouveau module pur include/automatism/reservoir_low_security.h
    (ReservoirLowSecurity::evaluate) : debounce (2 verrou / 3 déverrou) + hystérésis
    + zone morte. Aucune dépendance Arduino/config -> testable g++.
    - handleRefillReservoirLowSecurity (automatism_refill.cpp) délègue la décision ;
2026-06-15 refactor(ffp5cs): C4 — interface IActuators (inversion de dépendance god-class) + FakeActuators testé
    Étape structurante du découpage de la god-class Automatism : casse le couplage direct
    Automatism -> SystemActuators concret. Comportement inchangé (dispatch virtuel sur le même objet).
    - Nouvelle interface include/iactuators.h : surface minimale (16 méthodes) consommée par le
    module automatism (vérifiée par grep exhaustif _acts./acts.). Stats pompe non incluses.
    - SystemActuators implémente IActuators (héritage + override). Strictement additif : les autres
    consommateurs (web_server, app_context, realtime_websocket, global acts) gardent le concret.
2026-06-15 refactor(ffp5cs): C4 — extrait RefillStart (décision démarrage remplissage, pur + tests)
    Contrôleur refill : le gating de démarrage de handleRefillAutomaticStart (chemin de SÉCURITÉ)
    est extrait en décision pure testable, désormais possible grâce à IActuators.
    - Nouveau module include/automatism/refill_start.h (RefillStart::evaluate) : Start / BlockReserveLow
    / None selon niveau aquarium/réserve, verrou, essais, mode manuel, pompe active. Aucune dépendance
    Arduino -> testable g++.
    - handleRefillAutomaticStart délègue la décision ; effets de bord (startTankPump, verrou, email,
2026-06-15 refactor(ffp5cs): C4 — interface IMailer (inversion de dépendance messagerie) + FakeMailer testé
    Étape structurante : abstrait Mailer derrière IMailer pour pouvoir tester l'orchestration
    qui envoie des mails (alertes, fin nourrissage, veille/réveil) sans ESP_Mail_Client/réseau.
    Même patron que IActuators. Comportement inchangé (dispatch virtuel sur le même objet).
    - Nouvelle interface include/imailer.h : surface minimale (send, sendAlert, sendSleepMail,
    sendWakeMail) consommée par le module automatism. En-tête léger (SensorReadings en fwd-decl,
    pas de config.h/ESP_Mail_Client ; seul défaut = littéral includeDetailedReport=false).
2026-06-15 refactor(ffp5cs): C4 — extrait FeedingFinalizeOrchestrator (sync fin de nourrissage, testable)
    Avant-dernière orchestration couplée matériel rendue testable nativement.
    Automatism::finalizeFeedingIfNeeded délègue la décision « quoi publier (auto/manuel)
    et quel résultat » à FeedingFinalizeOrchestrator::run, testable via FakeStatusPublisher.
    Approche scopée & peu invasive (1 seule petite interface + params + Outcome) :
    - nouvelle interface MINIMALE include/istatus_publisher.h (publish(SensorReadings&, extraPairs)) ;
    Automatism l'implémente via un mince adaptateur nested forwardant vers sendFullUpdate.
2026-06-16 fix(ffp5cs): concurrence — états partagés multi-tâches en std::atomic (anti-course)
    Convertit trois états mutables partagés, accédés depuis plusieurs tâches FreeRTOS
    sans sérialisation, en std::atomic (style aligné sur net_request_pool.cpp et
    s_heartbeatDroppedCount). Strictement préservateur de comportement, diff minimal.
    - app_tasks.cpp s_bootConfigFetchDone : écrit par netTask (markBootConfigFetchDone),
    lu par loopTask/setup (waitForBootConfigFetch via postConfiguration). volatile -> atomic<bool>.
    - app_tasks.cpp s_wakeProtectionStartMs : écrit par autoTask (markWakeProtectionStart
2026-06-16 docs(ffp5cs): BACKLOG §12 — 3 chantiers // (ClockDecision + atomics + mutex cache distant)
    Documente les 3 PR draft parallèles (fichiers disjoints) : §12.a extraction pure ClockDecision
    (power.cpp, testée + brute-force), §12.b atomics anti-course (s_bootConfigFetchDone /
    s_wakeProtectionStartMs / s_nextSeq), §12.c mutex dédié s_remoteJsonCache (course config distante
    confirmée). Toutes VALIDATION BANC REQUISE.
    https://claude.ai/code/session_01HqRLTTnnpqYD2iWVL9ymso
2026-06-16 test(ffp5cs): couverture native de modules purs non testés
    Ajoute des suites Unity natives pour des modules de logique pure jusque-là
    non couverts (tests uniquement, aucune modification de code de production) :
    - test_board_traits_default / test_board_traits_s3beta : BoardTraits
    (board_traits.h), 13 prédicats constexpr carte/profil/endpoints utilisés
    dans tout le firmware. Les deux suites couvrent respectivement les branches
    « false » (aucune macro définie) et « true » (BOARD_S3/PSRAM/BETA/endpoints),
